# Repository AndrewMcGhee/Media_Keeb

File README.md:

# 2x3 Media Keypad - README

## Overview

The 2x3 Media Keypad is a compact, custom-built keyboard designed specifically for controlling media functions on your computer. With six programmable keys arranged in a 2x3 grid, this keypad allows you to easily manage tasks like play/pause, volume control, and track navigation. This README file provides information on assembling, programming, and using your 2x3 Media Keypad.

## Features

- **Compact Design:** A 2x3 grid layout that saves space on your desk.
- **Programmable Keys:** Customize each key to perform specific media functions.
- **USB Connectivity:** Easy to connect and use with most computers.
- **Plug-and-Play:** No special software required for basic media functions.

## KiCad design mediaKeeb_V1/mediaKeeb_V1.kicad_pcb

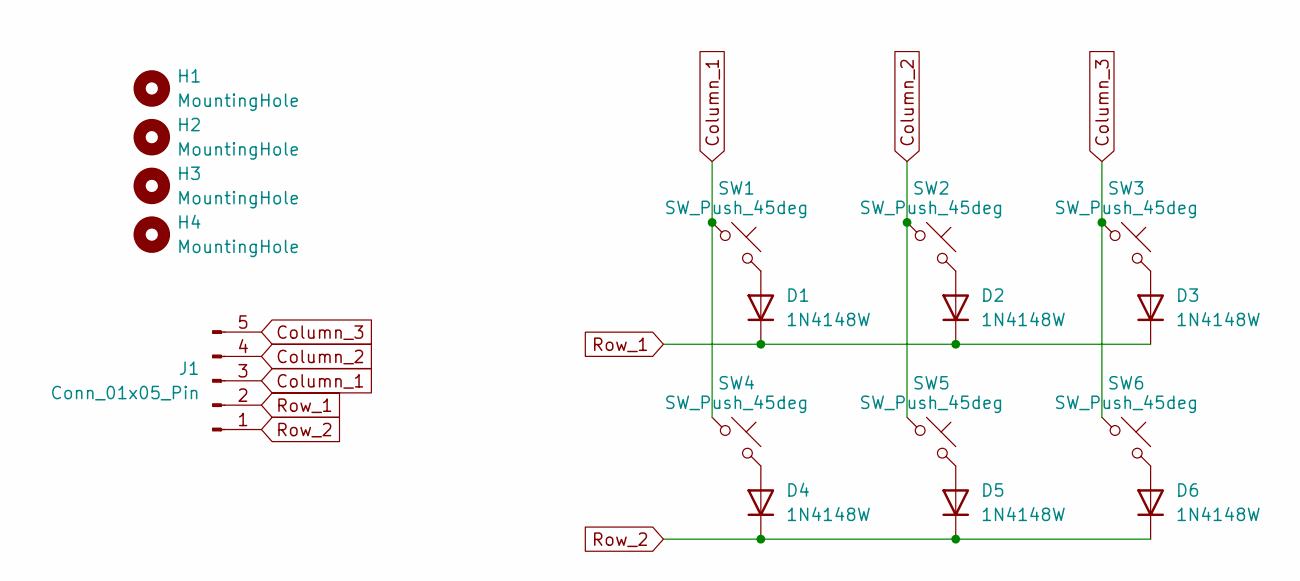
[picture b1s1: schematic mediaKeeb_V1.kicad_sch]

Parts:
D1, D2, D3, D4, D5, D6: 1N4148W; D_SOD-123
H1, H2, H3, H4: MountingHole; MountingHole_3.2mm_M3
J1: Conn_01x05_Pin; PinHeader_1x05_P2.54mm_Vertical
SW1, SW2, SW3, SW4, SW5, SW6: SW_Push_45deg; SW_Cherry_MX_PCB_1.00u

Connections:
Column_1: J1.3, SW1.1, SW4.1
Column_2: J1.4, SW2.1, SW5.1
Column_3: J1.5, SW3.1, SW6.1
unnamed: D1.2 (A), SW1.2
unnamed: D2.2 (A), SW2.2
unnamed: D3.2 (A), SW3.2
unnamed: D4.2 (A), SW4.2
unnamed: D5.2 (A), SW5.2
unnamed: D6.2 (A), SW6.2
Row_1: D1.1 (K), D2.1 (K), D3.1 (K), J1.2
Row_2: D4.1 (K), D5.1 (K), D6.1 (K), J1.1

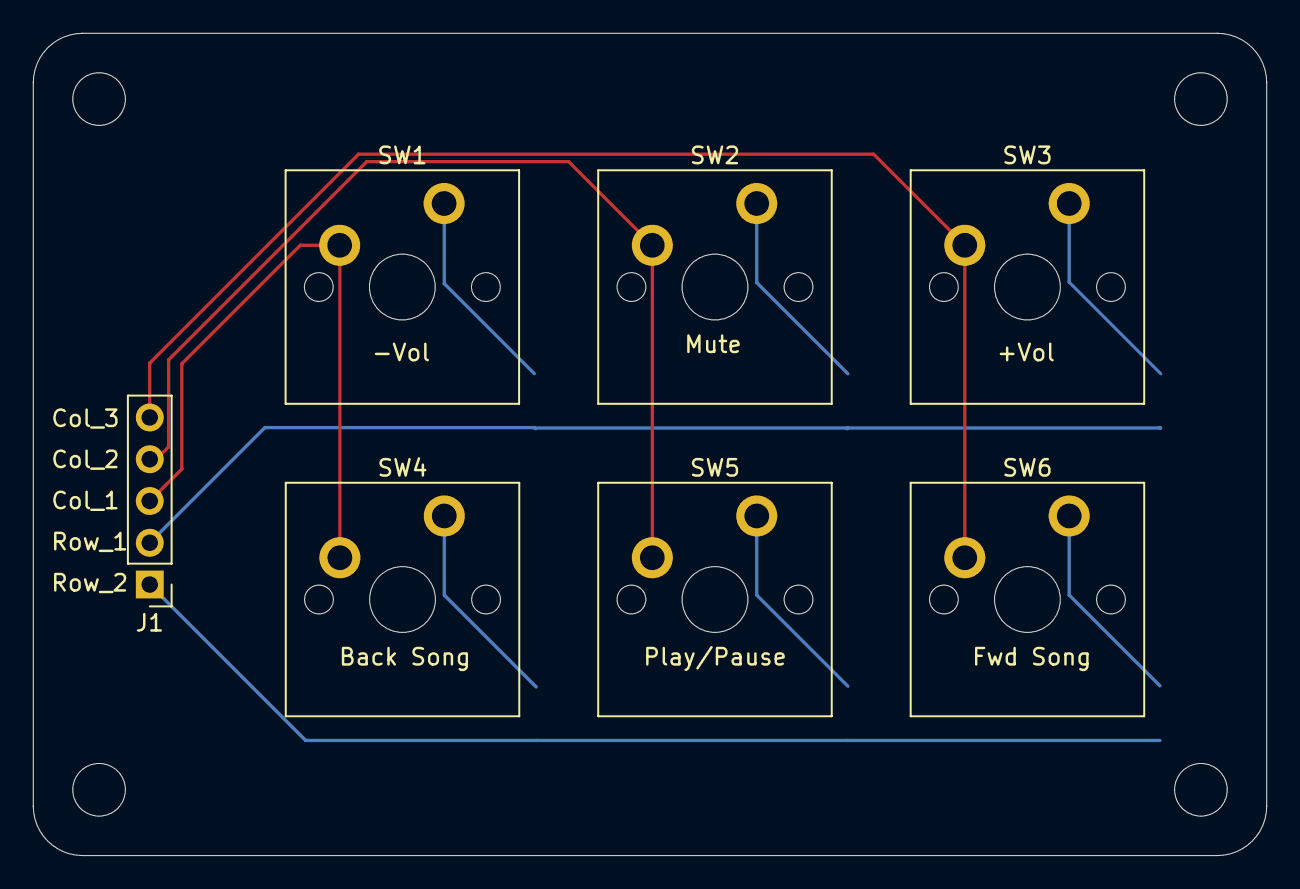
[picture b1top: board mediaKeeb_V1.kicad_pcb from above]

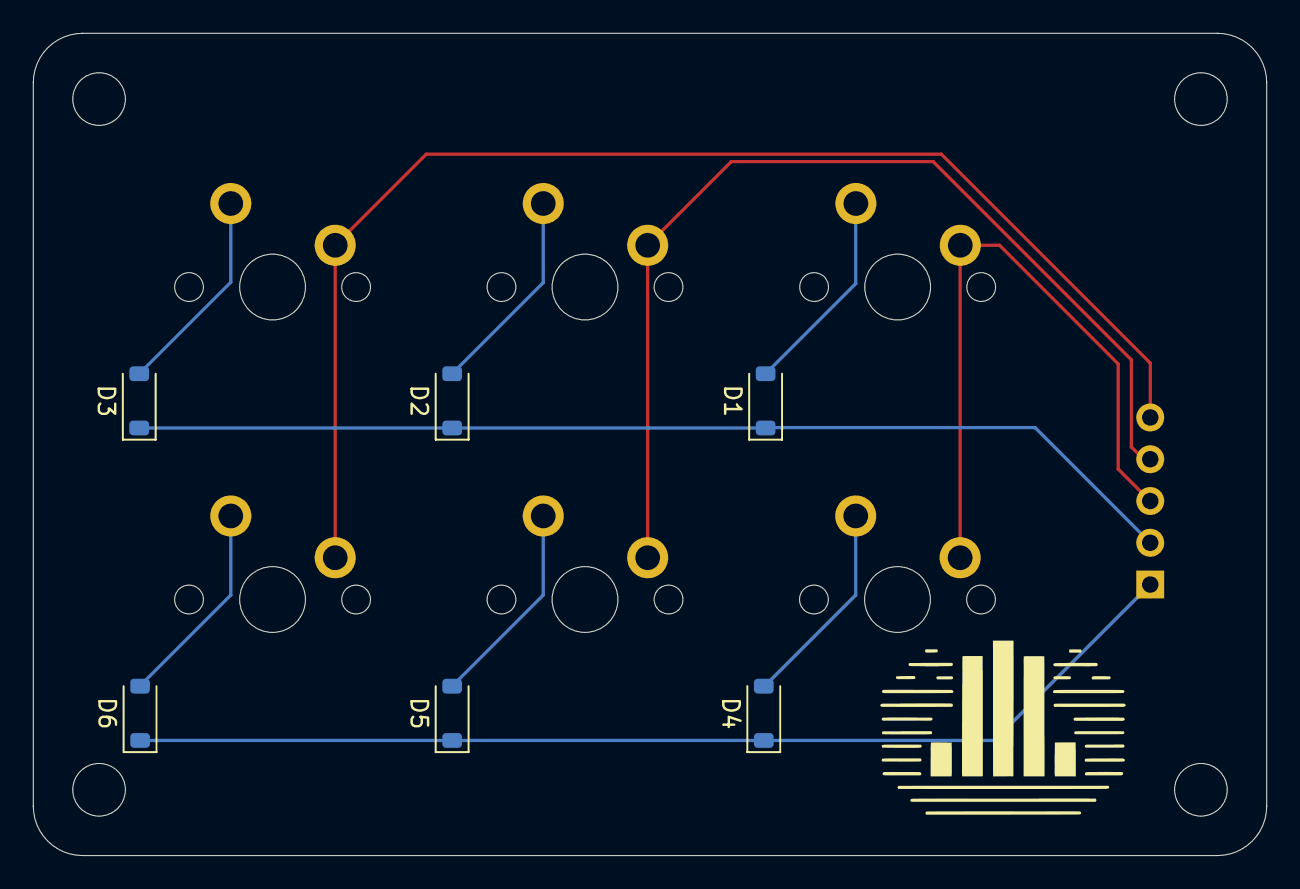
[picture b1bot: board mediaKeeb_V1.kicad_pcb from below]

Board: 2 copper layers, 75.0 x 50.0 mm, 17 parts (6 on the bottom side), 11 nets.

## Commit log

2024-03-12 Finished Rev1
    Ordered it and components for initial testing.
2024-03-12 :shrug:
2024-03-27 Rev2 Begin
2024-05-31 Updates Parts for V2
2024-05-31 Fix a stupid mistake
